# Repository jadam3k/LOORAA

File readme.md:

# LOORAAA!

LOORAAA! is a small LoRa module I designed myself, based on the general idea of the LoRa Puck. I didn’t copy the board — I recreated the design in my own way and added a few small changes, mainly status LEDs, so it’s actually useful during testing and debugging.

The board is built around the RP2040 and SX1262 and is designed to work on European LoRa frequencies. The main goal of this project was simple: design a complete RF board from scratch, understand what’s going on, and end up with something that actually works and can be reused in future projects.

## Why I Made This

I wanted real experience with RF design instead of just using ready-made modules. LoRa is widely used in IoT and long-range communication, and I thought combining it with the RP2040 would make a flexible and powerful base for future ideas.

This project was mainly about learning by doing — designing the schematic, routing RF properly, checking power integrity, and making sure everything makes sense together.

## What It Is

LOORAAA! is a compact LoRa communication module. It can transmit and receive LoRa packets over long distances and can be integrated into other embedded systems.

It includes external flash memory, proper power regulation, RF switching, and LEDs for status indication.

## Main Components

- **RP2040** – Dual-core Cortex-M0+ microcontroller running up to 133 MHz. It handles all logic and communication.
- **SX1262** – LoRa transceiver for long-range, low-power wireless communication (EU bands).
- **0900FM15K0039001E** – RF crystal oscillator for stable timing.
- **W25Q128JVS** – 128 Mbit SPI flash memory for additional storage.
- **AP2112K-3.3** – 3.3V voltage regulator.
- **PE4259** – RF switch between antenna and transceiver.
- Status LEDs – added by me for visibility and easier debugging.

## PCB

The PCB was designed entirely by me in KiCad.

It’s a 4-layer board. Two layers are mainly used for routing. I followed general RF layout practices (short RF traces, proper grounding, reasonable impedance handling).

This isn’t a hyper-optimized RF design for extreme environments — it’s a practical, working board designed carefully for real-world use.

## BOM

| Item | Description | Quantity | Total Price (USD) | URL |
|------|------------|----------|-------------------|-----|
| 100nF 0402 Capacitor | Ceramic capacitor 100nF 0402 package | 12 | SET | https://pl.aliexpress.com/item/1005010535197475.html |
| 1uF 0402 Capacitor | Ceramic capacitor 1uF 0402 package | 2 | SET | https://pl.aliexpress.com/item/1005010535197475.html |
| 15pF 0402 Capacitor | Ceramic capacitor 15pF 0402 package | 2 | SET | https://www.aliexpress.com/item/1005010535197475.html |
| 10uF 0402 Capacitor | Ceramic capacitor 10uF 0402 package | 2 | SET | https://www.aliexpress.com/item/1005010535197475.html |
| 1nF 0402 Capacitor | Ceramic capacitor 1nF 0402 package | 1 | SET | https://www.aliexpress.com/item/1005010535197475.html |
| 39pF 0402 Capacitor | Ceramic capacitor 39pF 0402 package | 1 | 0.53 | https://www.aliexpress.com/item/1005008550675610.html |
| 3.3pF 0402 Capacitor | Ceramic capacitor 3.3pF 0402 package | 2 | 0.66 | https://www.aliexpress.com/item/1005008550675610.html |
| 470nF 0402 Capacitor | Ceramic capacitor 470nF 0402 package | 1 | SET | https://www.aliexpress.com/item/1005010535197475.html |
| 47pF 0402 Capacitor | Ceramic capacitor 47pF 0402 package | 1 | SET | https://www.aliexpress.com/item/1005010535197475.html |
| 47nF 0402 Capacitor | Ceramic capacitor 47nF 0402 package | 1 | SET | https://www.aliexpress.com/item/1005010535197475.html |
| Green LED 0402 | Green indicator LED 0402 | 1 | 0.25 | https://www.digikey.pl/pl/products/detail/vishay-semiconductor-opto-division/VLMG1500-GS08/3504679 |
| Red LED 0402 | Red indicator LED 0402 | 1 | 0.18 | https://www.digikey.pl/pl/products/detail/liteon/LTST-C281KRKT/3198723 |
| Blue LED 0402 | Blue indicator LED 0402 | 1 | 0.26 | https://www.digikey.pl/pl/products/detail/qt-brightek-qtb/QBLP595-IB/6201906 |
| BLM15AX102SN1D | Ferrite bead 1kΩ @100MHz 0402 | 1 | 0.10 | https://www.digikey.pl/pl/products/detail/murata-electronics/BLM15AX102SN1D/2256877 |
| 0900FM15K0039001E | LoRa RF front-end filter | 1 | 0.46 | https://www.digikey.pl/pl/products/detail/johanson-technology-inc/0900FM15K0039001E/16639329 |
| USB4105-xx-A | USB-C receptacle USB2.0 16P | 1 | 0.49 | https://www.digikey.pl/pl/products/detail/gct/USB4215-03-A/24395489 |
| U.FL-R-SMT-1 | U.FL coaxial connector vertical | 1 | 1.29 | https://www.digikey.pl/pl/products/detail/hirose-electric-co-ltd/U-FL-R-SMT-1-10/2391570 |
| 15uH 0402 Inductor | Power inductor 15uH 0402 | 1 | 17.01 | https://www.aliexpress.com/item/1005010429708928.html |
| 47nH 0402 Inductor | RF inductor 47nH 0402 | 1 | 0.10 | https://www.digikey.pl/pl/products/detail/johanson-technology-inc/LRC0402CJ47NGV001T/1561270 |
| 9.1nH 0402 Inductor | RF inductor 9.1nH 0402 | 1 | 0.11 | https://www.aliexpress.com/item/1005003076582674.html |
| 400Ω 0402 Resistor | Resistor 400Ω 0402 | 3 | 0.28 | https://www.aliexpress.com/item/1005008851185252.html |
| 100Ω 0402 Resistor | Resistor 100Ω 0402 | 1 | 0.28 | https://www.aliexpress.com/item/1005008851185252.html |
| 10kΩ 0402 Resistor | Resistor 10kΩ 0402 | 1 | 0.28 | https://www.aliexpress.com/item/1005008851185252.html |
| 27.4Ω 0402 Resistor | Resistor 27.4Ω 0402 | 2 | 0.20 | https://www.digikey.pl/pl/products/detail/yageo/RC0402FR-0727R4L/5280945 |
| 1kΩ 0402 Resistor | Resistor 1kΩ 0402 | 2 | 0.28 | https://www.aliexpress.com/item/1005008851185252.html |
| 5.1kΩ 0402 Resistor | Resistor 5.1kΩ 0402 | 2 | 0.28 | https://www.aliexpress.com/item/1005008851185252.html |
| PTS636Sx25SMTRLFS | Reset tactile switch | 1 | 0.23 | https://www.digikey.pl/pl/products/detail/c-k/PTS636SK25SMTR-LFS/10071735 |
| PTS636Sx25SMTRLFS | SQPI tactile switch | 1 | 0.23 | https://www.digikey.pl/pl/products/detail/c-k/PTS636SK25SMTR-LFS/10071735 |
| SX1262IMLTRT | LoRa transceiver IC (QFN-24) | 1 | 7.60 | https://www.digikey.pl/pl/products/detail/semtech-corporation/SX1262IMLTRT/8564369 |
| RP2040 | Microcontroller QFN-56 | 1 | 0.70 | https://www.digikey.pl/pl/products/detail/raspberry-pi/SC0914-13/14306010 |
| W25Q128JVS | SPI Flash 128Mbit SOIC-8 | 1 | 0.72 | https://www.aliexpress.com/item/1005007401687554.html |
| AP2112K-3.3 | 3.3V LDO regulator SOT-23-5 | 1 | 1.76 | — |
| PE4259 | RF switch SC-70-6 | 1 | 0.79 | https://www.digikey.pl/pl/products/detail/psemi/4259-63/2614473 |
| 32MHz Crystal | SMD crystal 32MHz 3225 | 1 | 0.43 | https://www.digikey.pl/pl/products/detail/abracon-llc/ABM8-32-000MHZ-B2-T/2001197 |
| 12MHz Crystal | Abracon ABM8G 12MHz crystal | 1 | 0.53 | https://www.digikey.pl/pl/products/detail/abracon-llc/ABM8-272-T3/22472366 |

---

##  Note for BOM
**SET = capacitor assortment set (~4 USD)**  
https://www.aliexpress.com/item/1005010535197475.html

**Whole cost +-105$**

**PCB = 13,30 DOLLARS**

## ScreenShots

## How to Use

1. Flash the firmware to the RP2040.
2. Connect an antenna.
4. Communicate with the module!!!

The LEDs indicate activity, which makes debugging much easier.

# Info for reviewers:

I’m aware that there may be minor imperfections related to impedance matching, trace spacing, or capacitor placement. However, this is not a communication module for an F-35 fighter jet — it’s a simple student project.

The project is finished, it works as intended, and it meets its practical goals. There’s always something that could be optimized further, but in this case nothing needs to be changed.

Sometimes less really is more ;*

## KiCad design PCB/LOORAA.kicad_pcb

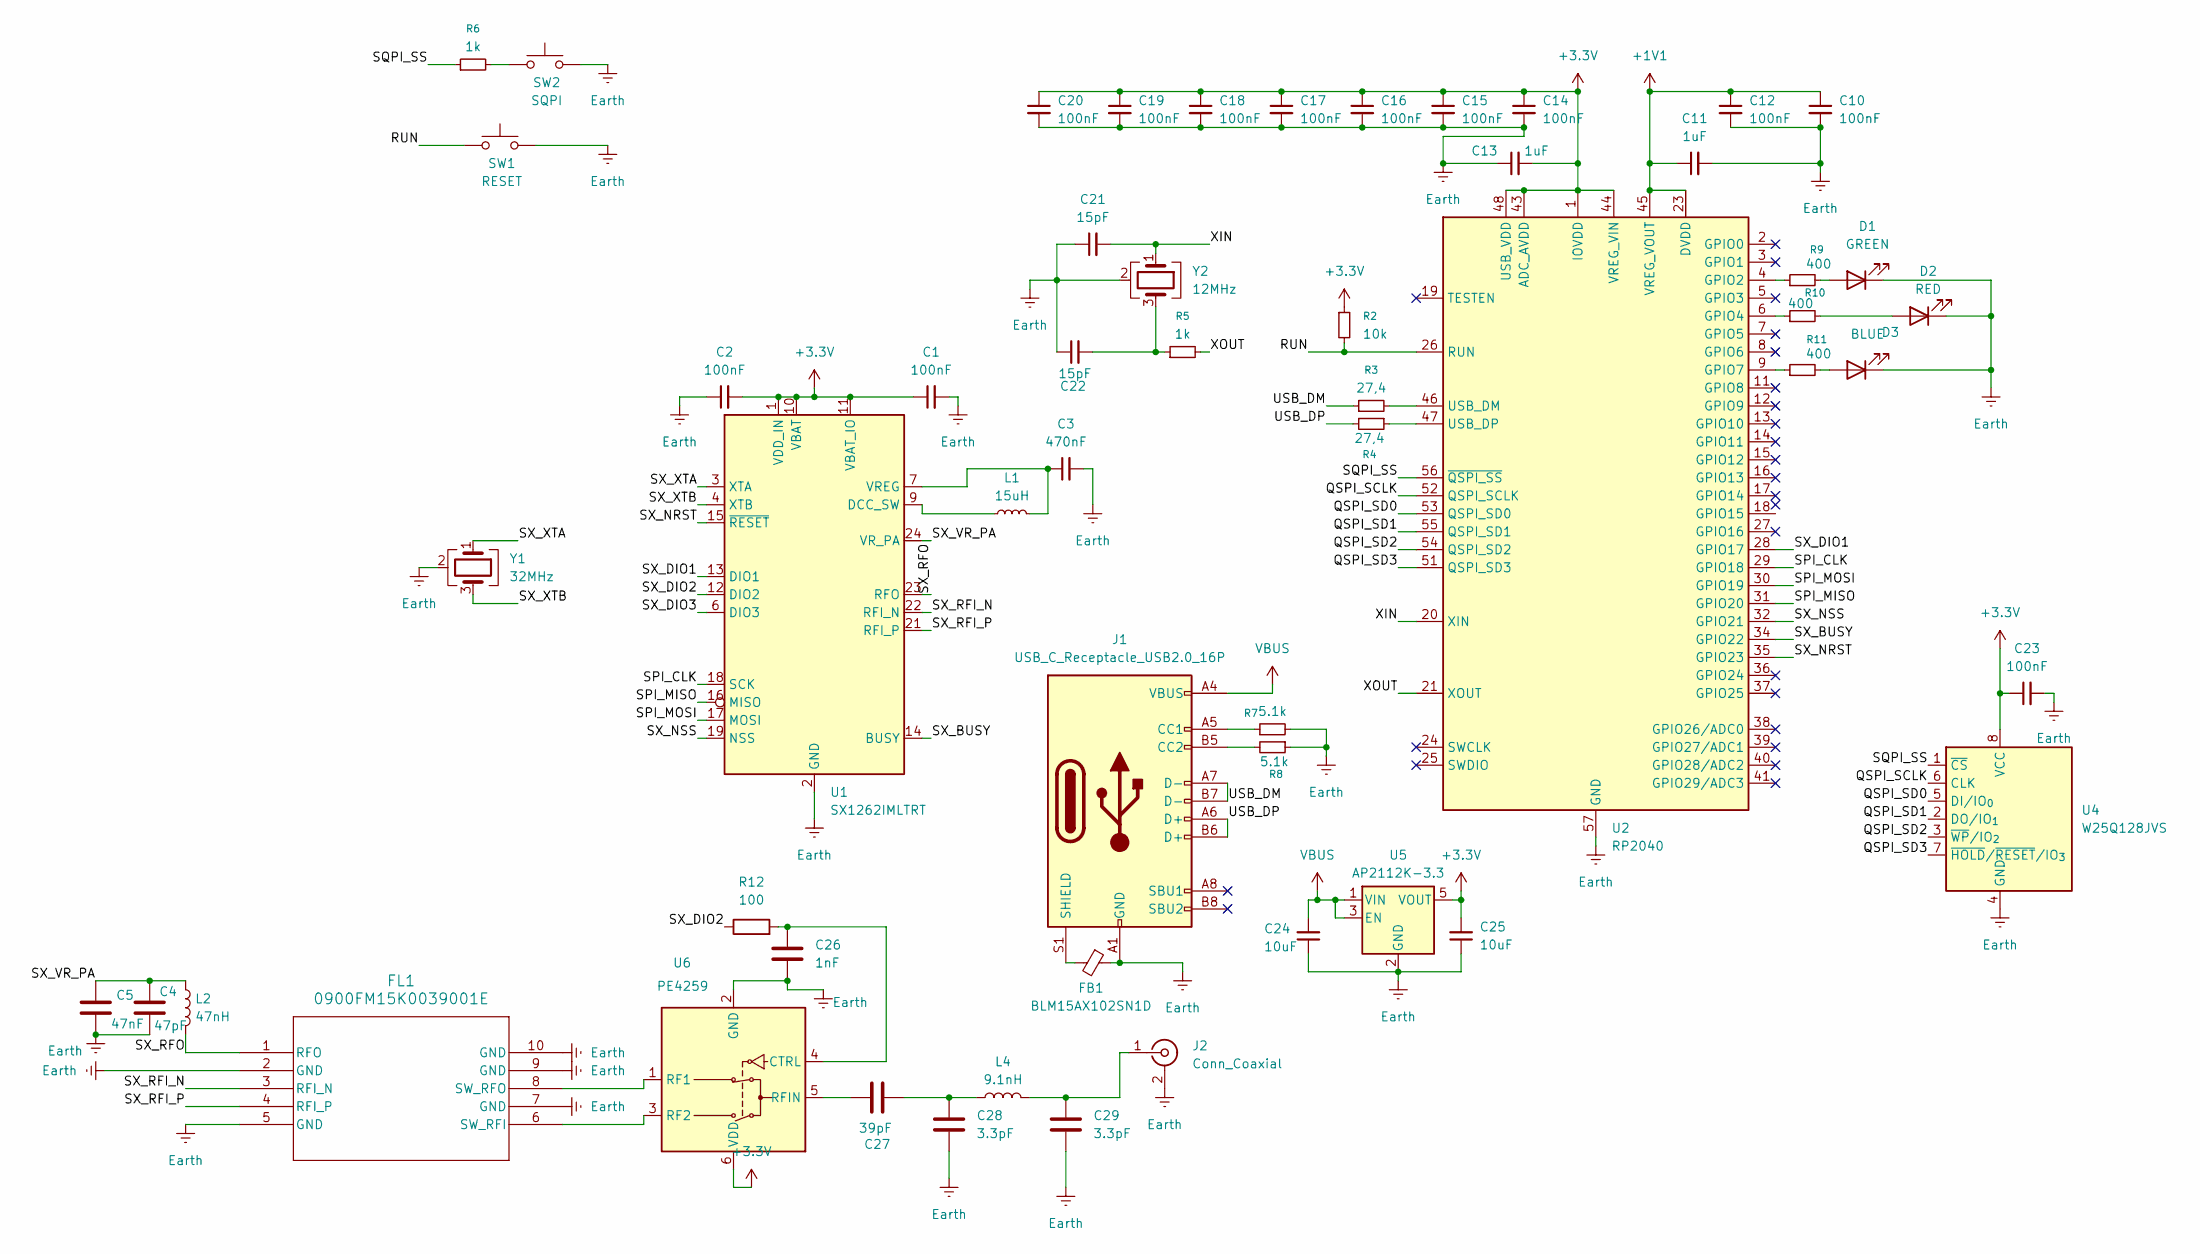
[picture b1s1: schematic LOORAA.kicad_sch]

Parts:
C1, C2, C10, C12, C14, C15, C16, C17, C18, C19, C20, C23: 100nF; C_0402_1005Metric
C3: 470nF; C_0402_1005Metric
C4: 47pF; C_0402_1005Metric
C5: 47nF; C_0402_1005Metric
C11, C13: 1uF; C_0402_1005Metric
C21, C22: 15pF; C_0402_1005Metric
C24, C25: 10uF; C_0402_1005Metric
C26: 1nF; C_0402_1005Metric
C27: 39pF; C_0402_1005Metric
C28, C29: 3.3pF; C_0402_1005Metric
D1: GREEN; LED_0402_1005Metric
D2: RED; LED_0402_1005Metric
D3: BLUE; LED_0402_1005Metric
FB1: BLM15AX102SN1D; L_0402_1005Metric
FL1: 0900FM15K0039001E; 0900FM15K0039001E_JOT
J1: USB_C_Receptacle_USB2.0_16P; USB_C_Receptacle_GCT_USB4105-xx-A_16P_TopMnt_Horizontal
J2: Conn_Coaxial; U.FL_Hirose_U.FL-R-SMT-1_Vertical
L1: 15uH; L_0402_1005Metric
L2: 47nH; L_0402_1005Metric
L4: 9.1nH; L_0402_1005Metric
R2: 10k; R_0402_1005Metric
R3, R4: 27,4; R_0402_1005Metric
R5, R6: 1k; R_0402_1005Metric
R7, R8: 5.1k; R_0402_1005Metric
R9, R10, R11: 400; R_0402_1005Metric
R12: 100; R_0402_1005Metric
SW1: RESET; SW_Tactile_SPST_NO_Straight_CK_PTS636Sx25SMTRLFS
SW2: SQPI; SW_Tactile_SPST_NO_Straight_CK_PTS636Sx25SMTRLFS
U1: SX1262IMLTRT; QFN-24-1EP_4x4mm_P0.5mm_EP2.6x2.6mm
U2: RP2040; QFN-56-1EP_7x7mm_P0.4mm_EP3.2x3.2mm
U4: W25Q128JVS; SOIC-8_5.3x5.3mm_P1.27mm
U5: AP2112K-3.3; SOT-23-5
U6: PE4259; SOT-363_SC-70-6
Y1: 32MHz; Crystal_SMD_3225-4Pin_3.2x2.5mm
Y2: 12MHz; Crystal_SMD_Abracon_ABM8G-4Pin_3.2x2.5mm

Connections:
+1V1: C10.1, C11.1, C12.1, U2.23 (DVDD), U2.45 (VREG_VOUT), U2.50 (DVDD)
+3.3V: C1.1, C2.2, C13.2, C14.1, C15.1, C16.1, C17.1, C18.1, C19.1, C20.1, C23.1, C25.2, R2.1, U1.1 (VDD_IN), U1.10 (VBAT), U1.11 (VBAT_IO), U2.1 (IOVDD), U2.10 (IOVDD), U2.22 (IOVDD), U2.33 (IOVDD), U2.42 (IOVDD), U2.43 (ADC_AVDD), U2.44 (VREG_VIN), U2.48 (USB_VDD), U2.49 (IOVDD), U4.8 (VCC), U5.5 (VOUT), U6.6 (VDD)
/QSPI_SCLK: U2.52 (QSPI_SCLK), U4.6 (CLK)
/QSPI_SD0: U2.53 (QSPI_SD0), U4.5 (DI/IO_{0})
/QSPI_SD1: U2.55 (QSPI_SD1), U4.2 (DO/IO_{1})
/QSPI_SD2: U2.54 (QSPI_SD2), U4.3 (~WP/IO_{2})
/QSPI_SD3: U2.51 (QSPI_SD3), U4.7 (~HOLD/~RESET/IO_{3})
/RUN: R2.2, SW1.1, U2.26 (RUN)
/SPI_CLK: U1.18 (SCK), U2.29 (GPIO18)
/SPI_MISO: U1.16 (MISO), U2.31 (GPIO20)
/SPI_MOSI: U1.17 (MOSI), U2.30 (GPIO19)
/SQPI_SS: R6.1, U2.56 (~QSPI_SS), U4.1 (~CS)
/SX_BUSY: U1.14 (BUSY), U2.34 (GPIO22)
/SX_DIO1: U1.13 (DIO1), U2.28 (GPIO17)
/SX_DIO2: R12.1, U1.12 (DIO2)
/SX_DIO3: U1.6 (DIO3)
/SX_NRST: U1.15 (~RESET), U2.35 (GPIO23)
/SX_NSS: U1.19 (NSS), U2.32 (GPIO21)
/SX_RFI_N: FL1.3 (RFI_N), U1.22 (RFI_N)
/SX_RFI_P: FL1.4 (RFI_P), U1.21 (RFI_P)
/SX_RFO: FL1.1 (RFO), L2.2, U1.23 (RFO)
/SX_VR_PA: C4.1, C5.1, L2.1, U1.24 (VR_PA)
/SX_XTA: U1.3 (XTA), Y1.1
/SX_XTB: U1.4 (XTB), Y1.3
/USB_DM: J1.A7 (D-), J1.B7 (D-), R3.1
/USB_DP: J1.A6 (D+), J1.B6 (D+), R4.2
/XIN: C21.2, U2.20 (XIN), Y2.1
/XOUT: R5.2, U2.21 (XOUT)
Earth: C1.2, C2.1, C3.2, C4.2, C5.2, C10.2, C11.2, C12.2, C13.1, C14.2, C15.2, C16.2, C17.2, C18.2, C19.2, C20.2, C21.1, C22.1, C23.2, C24.1, C25.1, C26.2, C28.2, C29.2, D1.1 (K), D2.1 (K), D3.1 (K), FB1.1, FL1.2 (GND), FL1.5 (GND), FL1.7 (GND), FL1.9 (GND), FL1.10 (GND), J1.A1 (GND), J1.A12 (GND), J1.B1 (GND), J1.B12 (GND), J2.2 (Ext), R7.2, R8.1, SW1.2, SW2.2, U1.2 (GND), U1.5 (GND), U1.8 (GND), U1.20 (GND), U1.25 (GND), U2.57 (GND), U4.4 (GND), U5.2 (GND), U6.2 (GND), Y1.2 (G), Y1.4 (G), Y2.2 (G), Y2.4 (G)
unnamed: C22.2, R5.1, Y2.3
unnamed: C27.2, C28.1, L4.1
unnamed: D1.2 (A), R9.2
unnamed: D2.2 (A), R10.2
unnamed: D3.2 (A), R11.2
unnamed: FL1.6 (SW_RFI), U6.3 (RF2)
unnamed: FL1.8 (SW_RFO), U6.1 (RF1)
unnamed: J1.A5 (CC1), R7.1
unnamed: J1.B5 (CC2), R8.2
unnamed: FB1.2, J1.S1 (SHIELD)
unnamed: C29.1, J2.1 (In), L4.2
unnamed: R6.2, SW2.1
unnamed: L1.1, U1.9 (DCC_SW)
unnamed: C3.1, L1.2, U1.7 (VREG)
unnamed: R9.1, U2.4 (GPIO2)
unnamed: R10.1, U2.6 (GPIO4)
unnamed: R11.1, U2.9 (GPIO7)
unnamed: R3.2, U2.46 (USB_DM)
unnamed: R4.1, U2.47 (USB_DP)
unnamed: C26.1, R12.2, U6.4 (CTRL)
unnamed: C27.1, U6.5 (RFIN)
VBUS: C24.2, J1.A4 (VBUS), J1.A9 (VBUS), J1.B4 (VBUS), J1.B9 (VBUS), U5.1 (VIN), U5.3 (EN)

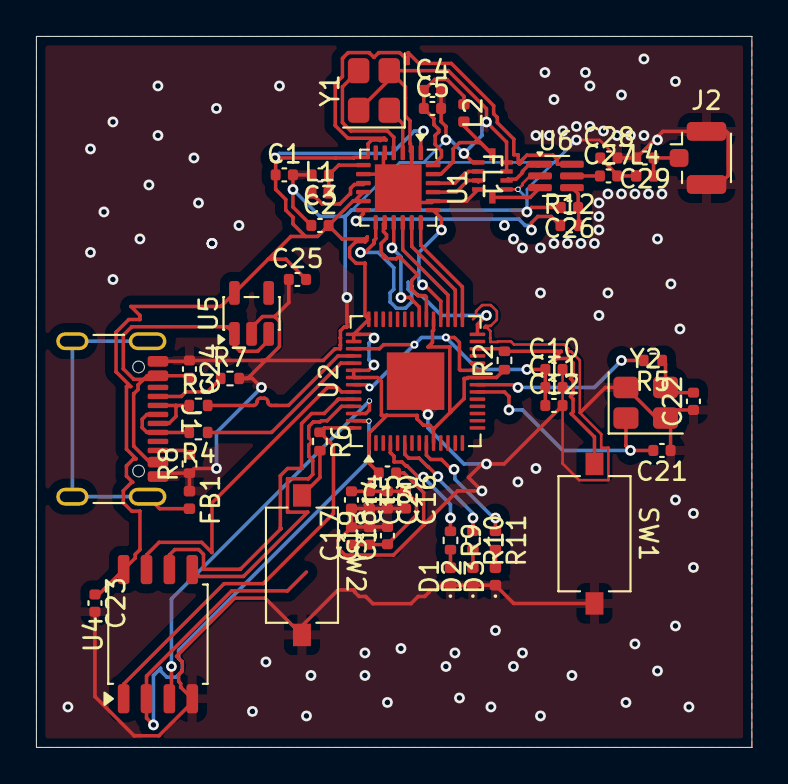
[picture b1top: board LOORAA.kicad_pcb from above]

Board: 4 copper layers, 39.8 x 39.5 mm, 55 parts (0 on the bottom side), 50 nets.

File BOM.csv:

Item,Description,Quantity,Total Price (USD),URL
100nF 0402 Capacitor,Ceramic capacitor 100nF 0402 package,12,SET,https://pl.aliexpress.com/item/1005010535197475.html?spm=a2g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
1uF 0402 Capacitor,Ceramic capacitor 1uF 0402 package,2,SET,https://pl.aliexpress.com/item/1005010535197475.html?spm=a2g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
15pF 0402 Capacitor,Ceramic capacitor 15pF 0402 package,2,SET,https://www.aliexpress.com/item/1005010535197475.html?spm=a2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
10uF 0402 Capacitor,Ceramic capacitor 10uF 0402 package,2,SET,https://www.aliexpress.com/item/1005010535197475.html?spm=a2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
1nF 0402 Capacitor,Ceramic capacitor 1nF 0402 package,1,SET,https://www.aliexpress.com/item/1005010535197475.html?spm=a2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
39pF 0402 Capacitor,Ceramic capacitor 39pF 0402 package,1,0.53,https://www.aliexpress.com/item/1005008550675610.html?spm=a2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
3.3pF 0402 Capacitor,Ceramic capacitor 3.3pF 0402 package,2,0.66,https://www.aliexpress.com/item/1005008550675610.html?spm=a2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
470nF 0402 Capacitor,Ceramic capacitor 470nF 0402 package,1,SET,https://www.aliexpress.com/item/1005010535197475.html?spm=a2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
47pF 0402 Capacitor,Ceramic capacitor 47pF 0402 package,1,SET,https://www.aliexpress.com/item/1005010535197475.html?spm=a2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
47nF 0402 Capacitor,Ceramic capacitor 47nF 0402 package,1,SET,https://www.aliexpress.com/item/1005010535197475.html?spm=a2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
Green LED 0402,Green indicator LED 0402,1,0.25,https://www.digikey.pl/pl/products/detail/vishay-semiconduct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
Red LED 0402,Red indicator LED 0402,1,0.18,https://www.digikey.pl/pl/products/detail/liteon/LTST-C281KR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
Blue LED 0402,Blue indicator LED 0402,1,0.26,https://www.digikey.pl/pl/products/detail/qt-brightek-qtb/QB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
BLM15AX102SN1D,Ferrite bead 1kΩ @100MHz 0402,1,0.10,https://www.digikey.pl/pl/products/detail/murata-electronics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
0900FM15K0039001E,LoRa RF front-end filter,1,0.46,https://www.digikey.pl/pl/products/detail/johanson-technolog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
USB4105-xx-A,USB-C receptacle USB2.0 16P,1,0.49,https://www.digikey.pl/pl/products/detail/gct/USB4215-03-A/24395489
U.FL-R-SMT-1,U.FL coaxial connector vertical,1,"1,29",https://www.digikey.pl/pl/products/detail/hirose-electric-co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
15uH 0402 Inductor,Power inductor 15uH 0402,1,17.01 (i cannot find anything cheaper ;*(,https://www.aliexpress.com/item/1005010429708928.html?spm=a2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
47nH 0402 Inductor,RF inductor 47nH 0402,1,0.10,https://www.digikey.pl/pl/products/detail/johanson-technolog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
9.1nH 0402 Inductor,RF inductor 9.1nH 0402,1,0.11,https://www.aliexpress.com/item/1005003076582674.html?spm=a2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
400Ω 0402 Resistor (used 390 its just only leds),Resistor 400Ω 0402,3,0.28,https://www.aliexpress.com/item/1005008851185252.html?spm=a2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
100Ω 0402 Resistor,Resistor 100Ω 0402,1,0.28,https://www.aliexpress.com/item/1005008851185252.html?spm=a2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
10kΩ 0402 Resistor,Resistor 10kΩ 0402,1,0.28,https://www.aliexpress.com/item/1005008851185252.html?spm=a2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
27.4Ω 0402 Resistor,Resistor 27.4Ω 0402,2,0.20,https://www.digikey.pl/pl/products/detail/yageo/RC0402FR-072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
1kΩ 0402 Resistor,Resistor 1kΩ 0402,2,0.28,https://www.aliexpress.com/item/1005008851185252.html?spm=a2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
5.1kΩ 0402 Resistor,Resistor 5.1kΩ 0402,2,0.28,https://www.aliexpress.com/item/1005008851185252.html?spm=a2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
PTS636Sx25SMTRLFS,Reset tactile switch,1,0.23,https://www.digikey.pl/pl/products/detail/c-k/PTS636SK25SMTR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
PTS636Sx25SMTRLFS,SQPI tactile switch,1,0.23,https://www.digikey.pl/pl/products/detail/c-k/PTS636SK25SMTR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
SX1262IMLTRT,LoRa transceiver IC (QFN-24),1,7.60,https://www.digikey.pl/pl/products/detail/semtech-corporatio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
RP2040,Microcontroller QFN-56,1,0.70,https://www.digikey.pl/pl/products/detail/raspberry-pi/SC091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
W25Q128JVS,SPI Flash 128Mbit SOIC-8,1,0.72,https://www.aliexpress.com/item/1005007401687554.html?spm=a2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
AP2112K-3.3,3.3V LDO regulator SOT-23-5,1,1.76,
PE4259,RF switch SC-70-6,1,0.79,https://www.digikey.pl/pl/products/detail/psemi/4259-63/2614473
32MHz Crystal,SMD crystal 32MHz 3225,1,0.43,https://www.digikey.pl/pl/products/detail/abracon-llc/ABM8-3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
12MHz Crystal,Abracon ABM8G 12MHz crystal,1,0.53,https://www.digikey.pl/pl/products/detail/abracon-llc/ABM8-2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
,,,SET = SETS OF CAPACITORS (BEST OPTION) 4 dollars,https://www.aliexpress.com/item/1005010535197475.html?spm=a2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

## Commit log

2026-02-13 final commit
2026-02-13 final commi3
2026-02-15 final commi33
2026-03-08 Add screenshots section to README
    Added screenshots to the README for better visualization.
